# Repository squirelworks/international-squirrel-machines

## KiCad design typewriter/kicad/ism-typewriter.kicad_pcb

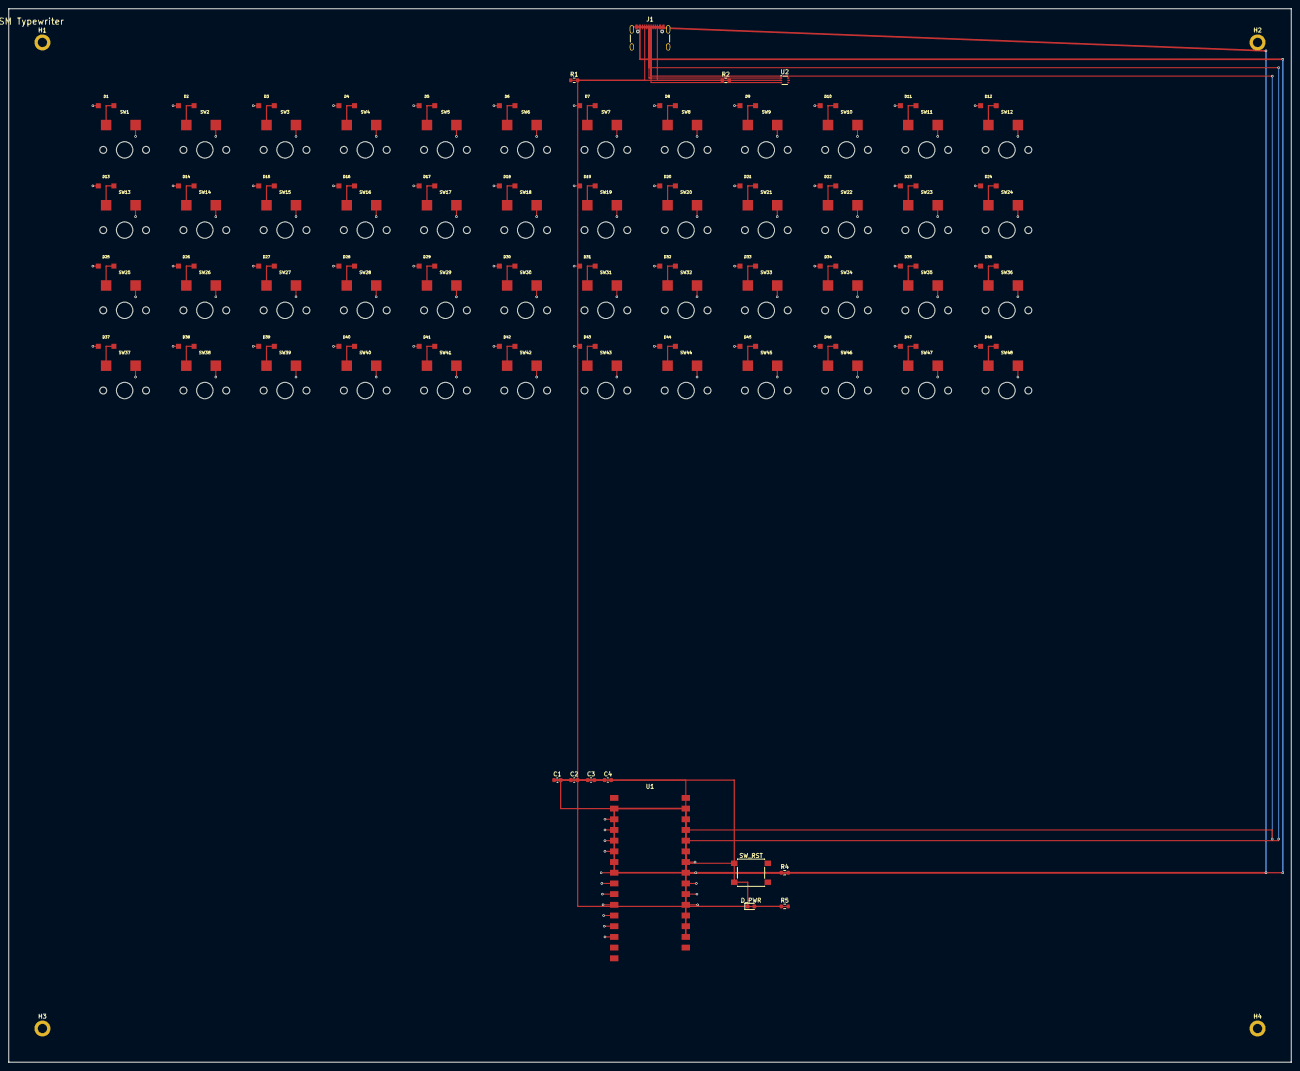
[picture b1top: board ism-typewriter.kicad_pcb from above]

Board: 4 copper layers, 304.6 x 250.2 mm, 113 parts (0 on the bottom side), 73 nets.

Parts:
C1, C2, C3, C4: 100nF; C_0603_1608Metric
D1, D2, D3, D4, D5, D6, D7, D8, D9, D10, D11, D12, D13, D14, D15, D16, D17, D18, D19, D20, D21, D22, D23, D24, D25, D26, D27, D28, D29, D30, D31, D32, D33, D34, D35, D36, D37, D38, D39, D40, D41, D42, D43, D44, D45, D46, D47, D48: 1N4148W; D_SOD123_nocrt
D_PWR: LED; LED_0603_1608Metric
H1, H2, H3, H4: M2; MountingHole_2.2mm_M2_DIN965_Pad
J1: USB_C; USB_C_Receptacle_GCT_USB4105-xx-A_16P_TopMnt_Horizontal
R1, R2: 5.1k; R_0603_1608Metric
R4: 10k; R_0603_1608Metric
R5: 1k; R_0603_1608Metric
SW1: ESC; SW_MX_Hotswap
SW2: Q; SW_MX_Hotswap
SW3: W; SW_MX_Hotswap
SW4: E; SW_MX_Hotswap
SW5: R; SW_MX_Hotswap
SW6: T; SW_MX_Hotswap
SW7: Y; SW_MX_Hotswap
SW8: U; SW_MX_Hotswap
SW9: I; SW_MX_Hotswap
SW10: O; SW_MX_Hotswap
SW11: P; SW_MX_Hotswap
SW12: BSPC; SW_MX_Hotswap
SW13: TAB; SW_MX_Hotswap
SW14: A; SW_MX_Hotswap
SW15: S; SW_MX_Hotswap
SW16: D; SW_MX_Hotswap
SW17: F; SW_MX_Hotswap
SW18: G; SW_MX_Hotswap
SW19: H; SW_MX_Hotswap
SW20: J; SW_MX_Hotswap
SW21: K; SW_MX_Hotswap
SW22: L; SW_MX_Hotswap
SW23: SCLN; SW_MX_Hotswap
SW24: RET; SW_MX_Hotswap
SW25: SHIFT; SW_MX_Hotswap
SW26: Z; SW_MX_Hotswap
SW27: X; SW_MX_Hotswap
SW28: C; SW_MX_Hotswap
SW29: V; SW_MX_Hotswap
SW30: B; SW_MX_Hotswap
SW31: N; SW_MX_Hotswap
SW32: M; SW_MX_Hotswap
SW33: COMM; SW_MX_Hotswap
SW34: DOT; SW_MX_Hotswap
SW35: SLSH; SW_MX_Hotswap
SW36: SHIFT2; SW_MX_Hotswap
SW37: CTRL; SW_MX_Hotswap
SW38: ALT; SW_MX_Hotswap
SW39: CAP; SW_MX_Hotswap
SW40: TAB2; SW_MX_Hotswap
SW41: SPC; SW_MX_Hotswap
SW42: SPC2; SW_MX_Hotswap
SW43: SPC3; SW_MX_Hotswap
SW44: MARGIN; SW_MX_Hotswap
SW45: BELL; SW_MX_Hotswap
SW46: COLOR; SW_MX_Hotswap
SW47: LF; SW_MX_Hotswap
SW48: CR; SW_MX_Hotswap
SW_RST: RESET; SW_SPST_PTS645
U1: RP2040_MOD; ISM_RP2040_Module
U2: USBLC6-2SC6; SOT-666

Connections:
+3V3: C1.1, C2.1, C3.1, C4.1, R4.2, R5.1, U1.14
+5V: J1.A4, J1.A9, J1.B4, J1.B9, U1.15, U2.5
CC1: J1.A5, R1.1
CC2: J1.B5, R2.1
COL0: D1.1, D13.1, D25.1, D37.1, U1.7
COL1: D2.1, D14.1, D26.1, D38.1, U1.8
COL2: D3.1, D15.1, D27.1, D39.1, U1.9
COL3: D4.1, D16.1, D28.1, D40.1, U1.10
COL4: D5.1, D17.1, D29.1, D41.1, U1.11
COL5: D6.1, D18.1, D30.1, D42.1, U1.12
COL6: D7.1, D19.1, D31.1, D43.1, U1.13
COL7: D8.1, D20.1, D32.1, D44.1, U1.19
COL8: D9.1, D21.1, D33.1, D45.1, U1.20
COL9: D10.1, D22.1, D34.1, D46.1, U1.21
COL10: D11.1, D23.1, D35.1, D47.1, U1.22
COL11: D12.1, D24.1, D36.1, D48.1, U1.23
GND: C1.2, C2.2, C3.2, C4.2, D_PWR.1, J1.A1, J1.A8, J1.A12, J1.B1, J1.B8, J1.B12, J1.S1, R1.2, R2.2, SW_RST.2, U1.1, U1.26, U2.2
LED_A: D_PWR.2, R5.2
NET_SW1: D1.2, SW1.2
NET_SW2: D2.2, SW2.2
NET_SW3: D3.2, SW3.2
NET_SW4: D4.2, SW4.2
NET_SW5: D5.2, SW5.2
NET_SW6: D6.2, SW6.2
NET_SW7: D7.2, SW7.2
NET_SW8: D8.2, SW8.2
NET_SW9: D9.2, SW9.2
NET_SW10: D10.2, SW10.2
NET_SW11: D11.2, SW11.2
NET_SW12: D12.2, SW12.2
NET_SW13: D13.2, SW13.2
NET_SW14: D14.2, SW14.2
NET_SW15: D15.2, SW15.2
NET_SW16: D16.2, SW16.2
NET_SW17: D17.2, SW17.2
NET_SW18: D18.2, SW18.2
NET_SW19: D19.2, SW19.2
NET_SW20: D20.2, SW20.2
NET_SW21: D21.2, SW21.2
NET_SW22: D22.2, SW22.2
NET_SW23: D23.2, SW23.2
NET_SW24: D24.2, SW24.2
NET_SW25: D25.2, SW25.2
NET_SW26: D26.2, SW26.2
NET_SW27: D27.2, SW27.2
NET_SW28: D28.2, SW28.2
NET_SW29: D29.2, SW29.2
NET_SW30: D30.2, SW30.2
NET_SW31: D31.2, SW31.2
NET_SW32: D32.2, SW32.2
NET_SW33: D33.2, SW33.2
NET_SW34: D34.2, SW34.2
NET_SW35: D35.2, SW35.2
NET_SW36: D36.2, SW36.2
NET_SW37: D37.2, SW37.2
NET_SW38: D38.2, SW38.2
NET_SW39: D39.2, SW39.2
NET_SW40: D40.2, SW40.2
NET_SW41: D41.2, SW41.2
NET_SW42: D42.2, SW42.2
NET_SW43: D43.2, SW43.2
NET_SW44: D44.2, SW44.2
NET_SW45: D45.2, SW45.2
NET_SW46: D46.2, SW46.2
NET_SW47: D47.2, SW47.2
NET_SW48: D48.2, SW48.2
ROW0: SW1.1, SW2.1, SW3.1, SW4.1, SW5.1, SW6.1, SW7.1, SW8.1, SW9.1, SW10.1, SW11.1, SW12.1, U1.2
ROW1: SW13.1, SW14.1, SW15.1, SW16.1, SW17.1, SW18.1, SW19.1, SW20.1, SW21.1, SW22.1, SW23.1, SW24.1, U1.3
ROW2: SW25.1, SW26.1, SW27.1, SW28.1, SW29.1, SW30.1, SW31.1, SW32.1, SW33.1, SW34.1, SW35.1, SW36.1, U1.4
ROW3: SW37.1, SW38.1, SW39.1, SW40.1, SW41.1, SW42.1, SW43.1, SW44.1, SW45.1, SW46.1, SW47.1, SW48.1, U1.5
RUN: R4.1, SW_RST.1, U1.18
USB_DM: J1.A7, J1.B7, U1.16, U2.3, U2.4
USB_DP: J1.A6, J1.B6, U1.17, U2.1, U2.6

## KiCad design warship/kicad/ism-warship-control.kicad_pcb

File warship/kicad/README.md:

# ISM Warship — KiCad (scale-model control) (#43)

Study-scale **ship control / trim logger** board for ISM-WS-1. Open with **KiCad 8**.

## Weapons boundary (hard)

- Outputs are **propulsion / steering / ballast actuator stubs** for a scale model only
- **No** weapons interfaces, fire control, seekers, guidance, warheads, or fuzing
- Combat topside remains mass/footprint placeholders in `../interfaces/mass-placeholders.yaml`

## Project-local libraries

| File | Role |
|------|------|
| `sym-lib-table` | Points at `ISM.kicad_sym` |
| `fp-lib-table` | Points at `ISM.pretty/` |
| `ISM.kicad_sym` | MCU, IMU, RADIO, CONN (actuator headers) |
| `ISM.pretty/` | Study footprints (same family as fighter bay study) |

## Schematic / PCB (`ism-warship-control`)

| Net / header | Role |
|--------------|------|
| I2C | IMU trim / attitude stub |
| SPI | Telemetry radio stub |
| J1 `PWM_PORT` | Port thruster / prop stub |
| J2 `PWM_STBD` | Starboard thruster stub |
| J3 `PWM_RUDDER` | Rudder servo stub |
| J4 `PWM_BALLAST` | Ballast / trim pump stub |
| 3V3 / 5V / GND | Rails with PWR_FLAG |

Study MCU footprint pitch is packaging-level (not production RP2040 0.4 mm).

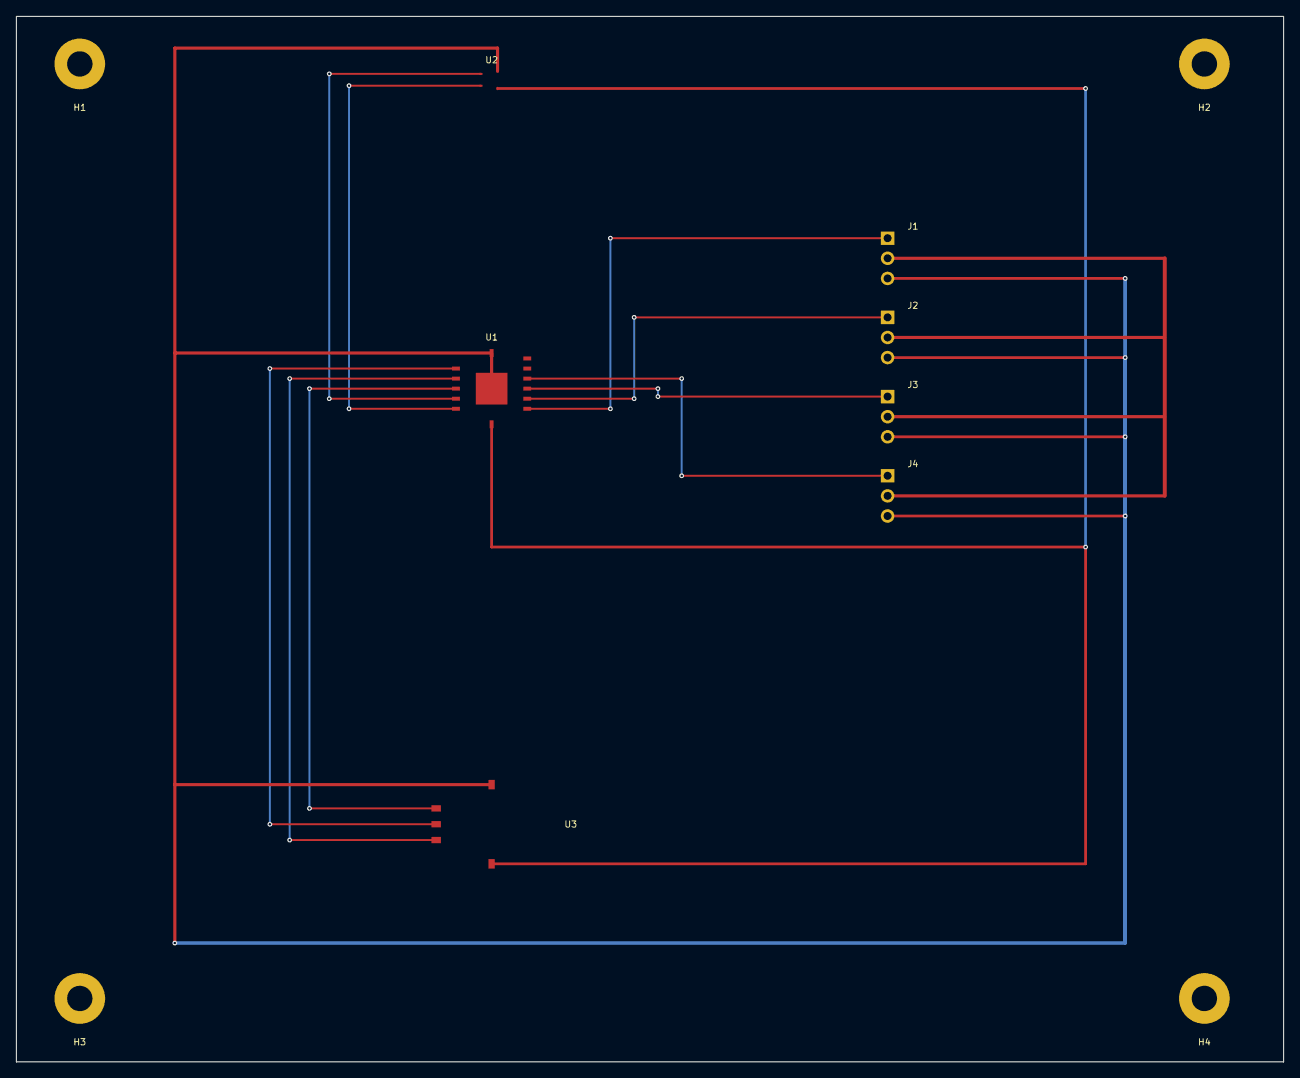
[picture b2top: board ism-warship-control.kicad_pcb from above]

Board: 2 copper layers, 160.0 x 132.0 mm, 11 parts (0 on the bottom side), 12 nets.

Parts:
H1, H2, H3, H4: M3; MountingHole_3.2mm_M3
J1: J1; PinHeader_1x03_P2.54mm
J2: J2; PinHeader_1x03_P2.54mm
J3: J3; PinHeader_1x03_P2.54mm
J4: J4; PinHeader_1x03_P2.54mm
U1: RP2040; QFN-56-1EP_7x7mm_P0.4mm
U2: IMU; LGA-14_3x2.5mm_P0.5mm
U3: RADIO; RADIO_Module

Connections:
3V3: U1.11, U2.4, U3.5
5V: J1.2, J2.2, J3.2, J4.2
GND: J1.3, J2.3, J3.3, J4.3, U1.10, U1.EP, U2.3, U3.4
I2C_SCL: U1.2, U2.2
I2C_SDA: U1.1, U2.1
PWM_BALLAST: J4.1, U1.9
PWM_PORT: J1.1, U1.6
PWM_RUDDER: J3.1, U1.8
PWM_STBD: J2.1, U1.7
SPI_MISO: U1.5, U3.2
SPI_MOSI: U1.4, U3.1
SPI_SCK: U1.3, U3.3

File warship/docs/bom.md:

# Warship — educational master BOM (#43)

**Product:** ISM-WS-1  
**Slice:** study BOM tying the scale-model control fab package to the hull STL / structural stubs.

## Scope limits (hard)

- Scale-model / educational packaging only
- Weapons and combat sensors = **mass / footprint** placeholders only (`../interfaces/mass-placeholders.yaml`)
- **No** weapons interfaces, fire control, seekers, guidance, warheads, or fuzing
- **No** ITAR/EAR content
- **Not** a procurement order — PNs freeze at inquire-for-release

## Board (SMT) — from `../fab/BOM.csv`

| Ref | Qty | Value | Role |
|-----|-----|-------|------|
| U1 | 1 | RP2040 | Scale-model MCU stub |
| U2 | 1 | IMU | Attitude stub |
| U3 | 1 | RADIO | Telemetry stub |
| J1 | 1 | PinHeader 1×03 | Port thruster PWM stub |
| J2 | 1 | PinHeader 1×03 | Stbd thruster PWM stub |
| J3 | 1 | PinHeader 1×03 | Rudder PWM stub |
| J4 | 1 | PinHeader 1×03 | Ballast/trim PWM stub |
| H1–H4 | 4 | M3 hole | Board mounting |

## Mechanical / study article

| ID | Qty | Item | Source |
|----|-----|------|--------|
| MECH-HULL-STL | 1 | `hull_study.stl` print (hull + ghost structure) | `../mechanical/` |
| MECH-SCAD | 1 | `hull_study.scad` parametric source | `../shell/` |
| MECH-FAST-M3 | lot | M3 hardware for control-board tray | study |
| MECH-TRAY | 1 | Control-board tray stub | `structural.yaml` |
| MASS-WPN | lot | Inert weapons mass boxes | `mass-placeholders.yaml` |
| MASS-SENS | lot | Inert combat-sensor mass boxes | `mass-placeholders.yaml` |

## Electrical harness (study)

| ID | Qty | Item | Notes |
|----|-----|------|-------|
| HAR-PORT | 1 | 3-pin PWM lead | J1 port thruster stub |
| HAR-STBD | 1 | 3-pin PWM lead | J2 stbd thruster stub |
| HAR-RUD | 1 | 3-pin PWM lead | J3 rudder stub |
| HAR-BAL | 1 | 3-pin PWM lead | J4 ballast/trim stub |
| HAR-PWR | 1 | 5 V / GND stub lead | Bench supply only |

## Out of BOM (explicit)

Weapons fire-control LRUs, seekers, guidance kits, warheads, fuzing/arming hardware, combat-system internals.
